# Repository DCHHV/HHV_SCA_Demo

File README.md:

# DEF CON Hardware Hacking Village Side Channel Attack Demo
This demo focuses on teaching and exploiting a simple timing attack vulnerable set up. It is a hardware device that consists of a PIC12F1572 (Enhanced Mid-range), 4 tactile buttons, LED indicators, an FTDI USB serial interface, and a connection for a logic analyzer (specifically a USBee AX PRO which the HHV has a small stock of). The demo is self-guided, that is, the serial interface provides instructions on each stage of the demo.

## About
The demo consists of 4 stages that become increasingly difficult. Each stage requires the user to identify a valid PIN for that stage. The PIN is a 4 digit, 4 value number; this provides 256 combinations. Due to the low complexity and lack of timeout penalty, brute forcing a PIN for each stage is reasonably possible but highly discouraged since the intent is to learn about side-channel attacks.

There are two LEDs, a red and a green, that flicker when the PIN is being input. The green LED turns on when a button is pressed, and off when it is released. Depending on the stage, once the full PIN is input, the red LED will flash if the pin was incorrect, or the green LED will turn solid for a few seconds if it was correct. The USB serial interface also has a red and green LED to indicate serial activity.

The digits of the PIN are connected to a single analog input of the PIC. Between the switches, a resistor ladder is set up. This allows for a consistent and unique analog voltage value for each digit. The analog input is polled at roughly 8 ms from the PIC (this timing has no bearing on the SCA demo or its vulnerabilities).

The red and green LEDs for the PIN input are connected to a 2x5 0.1" female header. A USBee AX PRO can be directly connected to this input. The LEDs are then connected to D0 and D1 of the logic analyzer. This logic analyzer is compatible with `sigrok`/`pulseview`, it is not a Saleae clone. Any other 3.3 V compatible logic analyzers can be used instead; it was highly convenient to use this pinout as the HHV has a stock of the USBee logic analyzers.

Note that we have observed that some models of Saleae clones actually work better in `pulseview` than the official Logic software. This may be due to a number of reasons, but it was found that in the Logic software both for Windows and Linux, a Saleae clone would often fail to run at 16 MHz. This failure was followed up with a comment to lower the sample rate and try again. Under `pulseview` for both Windows and Linux however, this device performed at the 16 MHz sample rate quite reliably. The USBee AX PRO is not a Saleae clone; this observervation is provided as a reference for using other logic analyzers.

A full breakdown of each stage, how the vulnerability works, step by step instructions, and proper mitigation techniques for this specific setup, are available in `docs/README.md`

## Setup
There is a specific order to the following steps, this is due to `pulseview` recognizing the FTDI device and attempting to utilize it as a logic analyzer interface. Doing this in any other order is possible but it becomes a hassle as `pulseview` tries to consume the USB serial device, even if it is already open in some cases.

1. Connect the USBee AX PRO to the host computer
2. Open `pulseview`. The tool should automatically detect and initialize the logic analyzer, if not, it can be manually set up by scanning for 'fx2lafw' devices. Note that on Linux based systems, there is a separate firmware package for the 'fx2lafw' firmware files.
3. Connect the FTDI USB serial cable (if this is connected before `pulseview` is started, then `pulseview` may try to claim the FTDI device)
4. Open a serial terminal to the just created USB terminal at 9600 baud, 8n1.
5. Press "RESET" button on the HHV SCA Demo board; text should appear on the terminal

## Build your own
All of the PCB sources for EagleCAD are available in the `eagle/` directory. The Gerber files are available in the `eagle/out/` directory and are named directly for use with OSHPark. Simply zip up the files and upload them. The Gerber files are also compatible with pretty much every PCB manufacturer as-is. A full BOM is also in the `eagle/` directory.

The PIC _can_ be programmed via the on-board ICSP header by connecting a PICKit device which supports PIC12F1572. However, we do not recommend connecting directly to this and instead recommend programming the microcontroller out of circuit. Due to conflicting driving signals, there are two marked pads that must be cut for ICSP operation. These must be bridged back together for normal operation.

The `HHV_SCA_Demo-production.hex` file can be directly written to the PIC12F1572.

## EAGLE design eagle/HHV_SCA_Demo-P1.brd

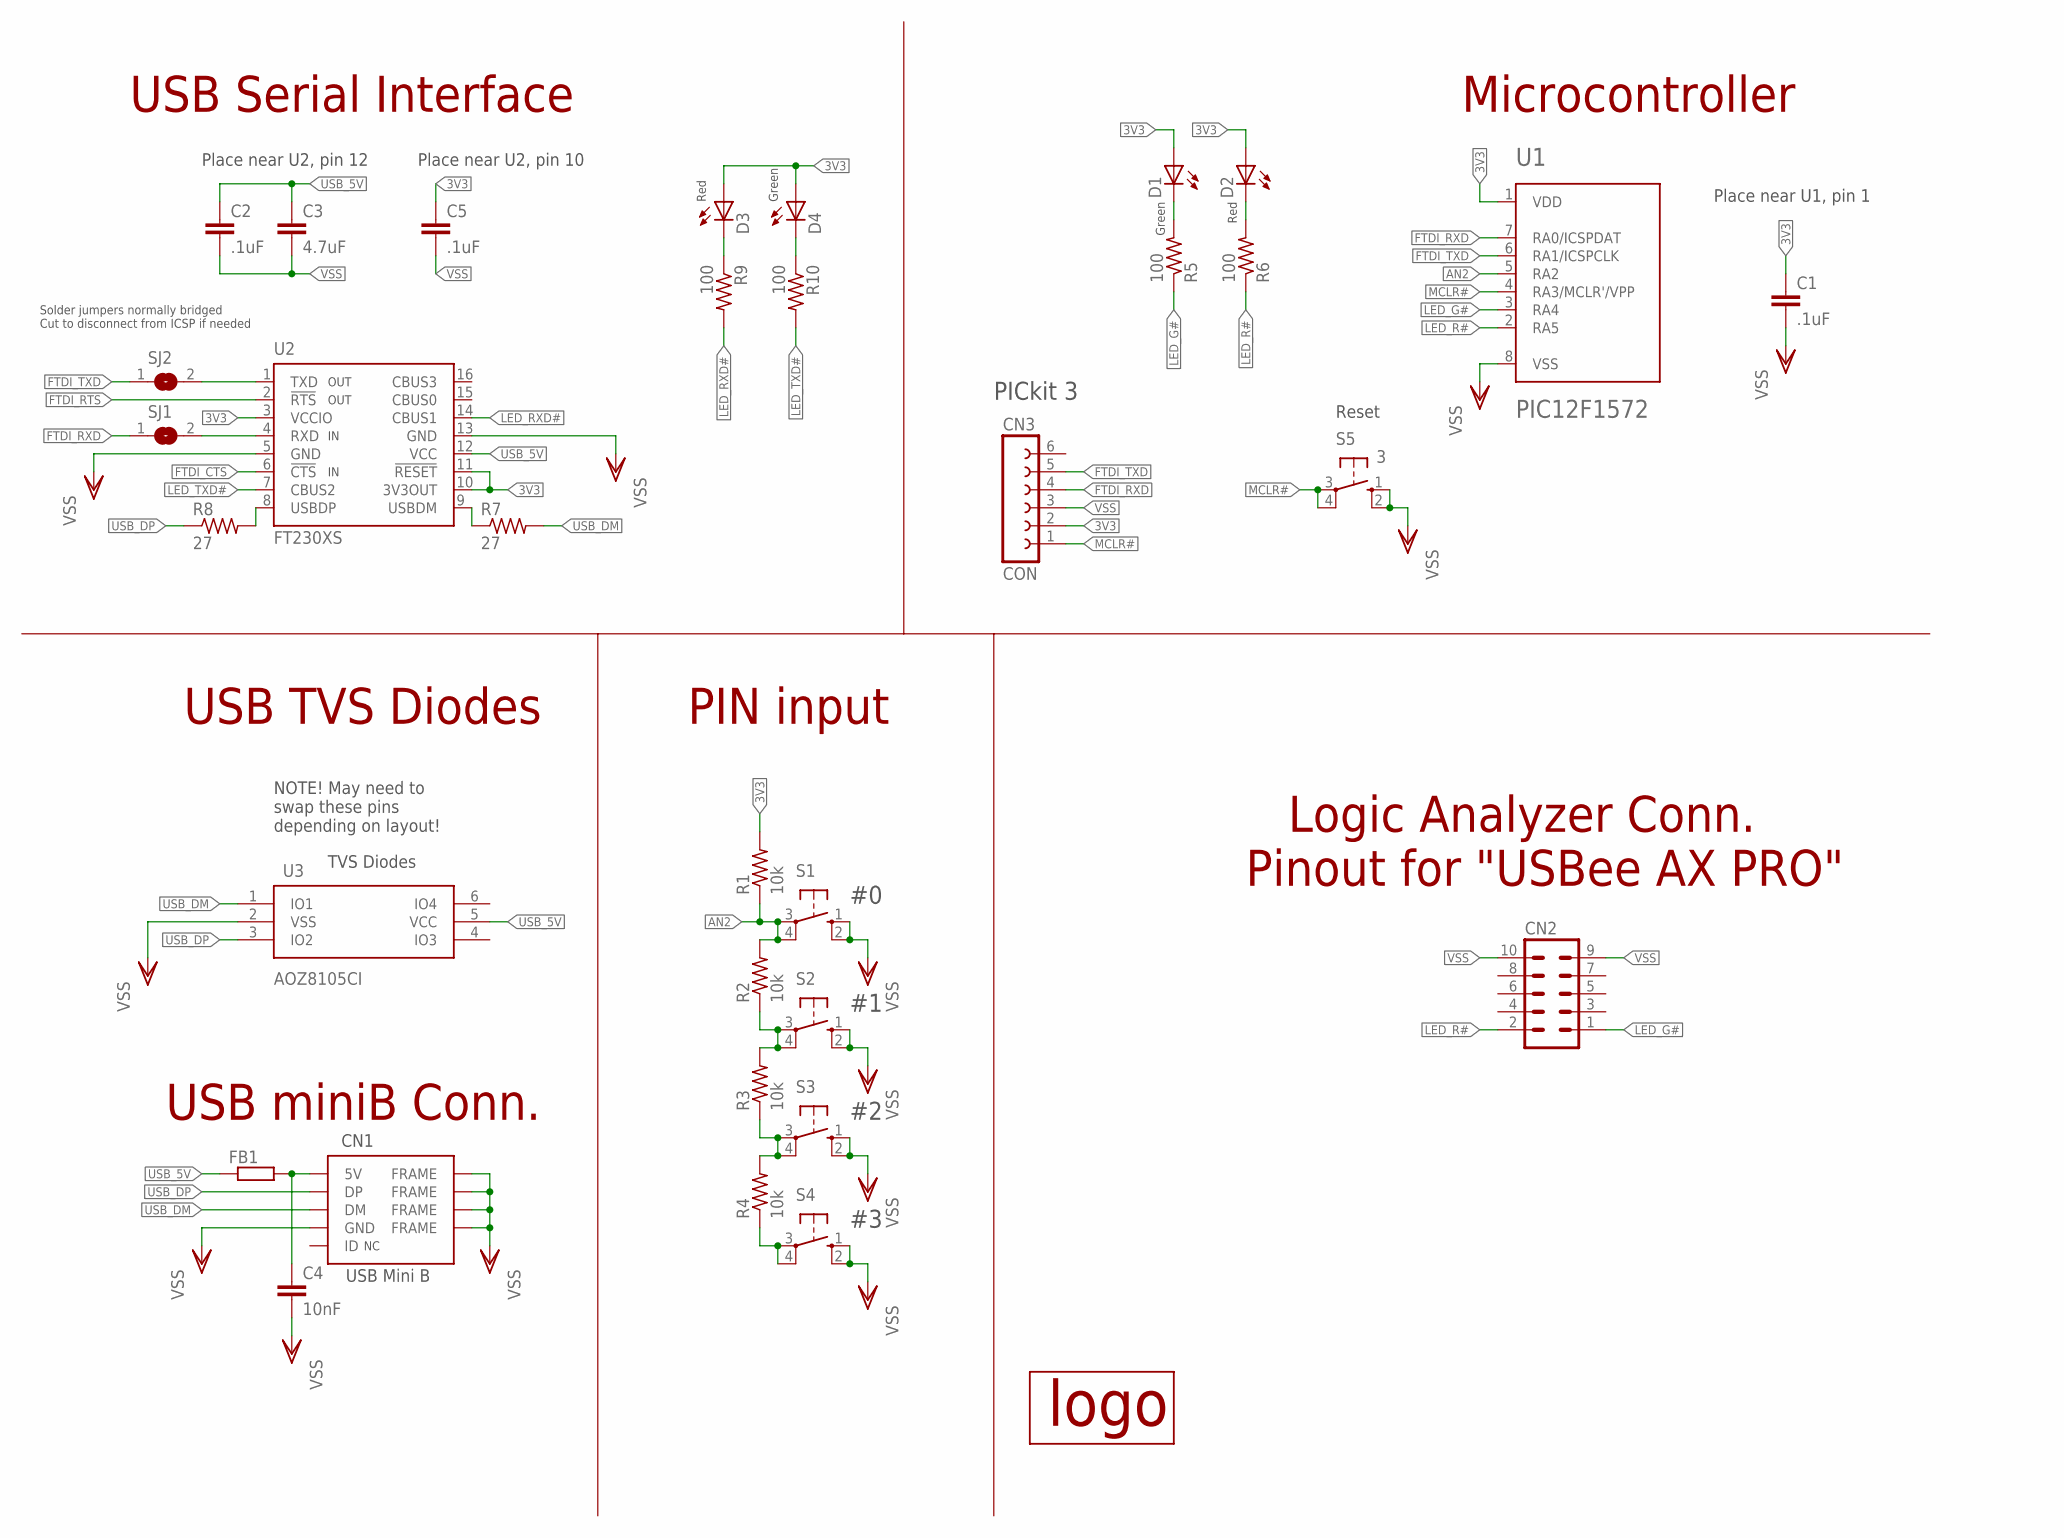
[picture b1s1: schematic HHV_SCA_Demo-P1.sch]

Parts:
C1, C2, C5: .1uF; C0603K
C3: 4.7uF; C0603K
C4: 10nF; C0603K
CN1: MINIUSB-SMD
CN2: MA05-2
CN3: CON; FE06
D1, D2, D3, D4: LED3MM
FB1: R-EU_R0603; R0603
R1, R2, R3, R4: 10k; R0603
R5, R6, R9, R10: 100; R0603
R7, R8: 27; R0402
S1, S2, S3, S4: 10-XX; B3F-10XX
S5: 3; B3F-10XX
SJ1, SJ2: SJ
U1: PIC12F1572; DIL8
U2: FT230XS; SSOP16
U3: AOZ8105CI; SOT23-6L
U$1: KBELOGO-SILK

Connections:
3V3: C1.1, C5.1, CN3.2, D1.A, D2.A, D3.A, D4.A, R1.2, U1.1 (VDD), U2.3 (VCCIO), U2.10 (3V3OUT), U2.11 (!RESET)
AN2: R1.1, R2.2, S1.3, S1.4 (P1), U1.5 (RA2)
FTDI_CTS: U2.6 (!CTS)
FTDI_RTS: U2.2 (!RTS)
FTDI_RXD: CN3.4, SJ1.1, U1.7 (RA0/ICSPDAT)
FTDI_TXD: CN3.5, SJ2.1, U1.6 (RA1/ICSPCLK)
LED_G#: CN2.1, R5.1, U1.3 (RA4)
LED_R#: CN2.2, R6.1, U1.2 (RA5)
LED_RXD#: R9.2, U2.14 (CBUS1)
LED_TXD#: R10.2, U2.7 (CBUS2)
MCLR#: CN3.1, S5.3, S5.4 (P1), U1.4 (RA3/MCLR'/VPP)
unnamed: R4.1, S4.3, S4.4 (P1)
unnamed: R3.1, R4.2, S3.3, S3.4 (P1)
unnamed: D2.K (C), R6.2
unnamed: R7.1, U2.9 (USBDM)
unnamed: R2.1, R3.2, S2.3, S2.4 (P1)
unnamed: R8.2, U2.8 (USBDP)
unnamed: D1.K (C), R5.2
unnamed: D3.K (C), R9.1
unnamed: C4.1, CN1.5V, FB1.2
unnamed: D4.K (C), R10.1
unnamed: SJ2.2, U2.1 (TXD)
unnamed: SJ1.2, U2.4 (RXD)
USB_5V: C2.1, C3.1, FB1.1, U2.12 (VCC), U3.5 (VCC)
USB_DM: CN1.USB_DM (DM), R7.2, U3.1 (IO1)
USB_DP: CN1.USB_DP (DP), R8.1, U3.3 (IO2)
VSS: C1.2, C2.2, C3.2, C4.2, C5.2, CN1.GND@0 (FRAME), CN1.GND@1 (FRAME), CN1.GND@2 (FRAME), CN1.GND@3 (FRAME), CN1.VSS (GND), CN2.9, CN2.10, CN3.3, S1.1 (S), S1.2 (S1), S2.1 (S), S2.2 (S1), S3.1 (S), S3.2 (S1), S4.1 (S), S4.2 (S1), S5.1 (S), S5.2 (S1), U1.8 (VSS), U2.5 (GND), U2.13 (GND), U3.2 (VSS)

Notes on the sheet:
OUT
Place near U2, pin 12
TVS Diodes
Place near U2, pin 10
CN1
USB Mini B
NOTE! May need to swap these pins depending on layout!
Red
Green
PICkit 3
Place near U1, pin 1
USB Serial Interface
USB TVS Diodes
USB miniB Conn.
Microcontroller
Reset
PIN input
Logic Analyzer Conn. Pinout for "USBee AX PRO"
Solder jumpers normally bridged Cut to disconnect from ICSP if needed

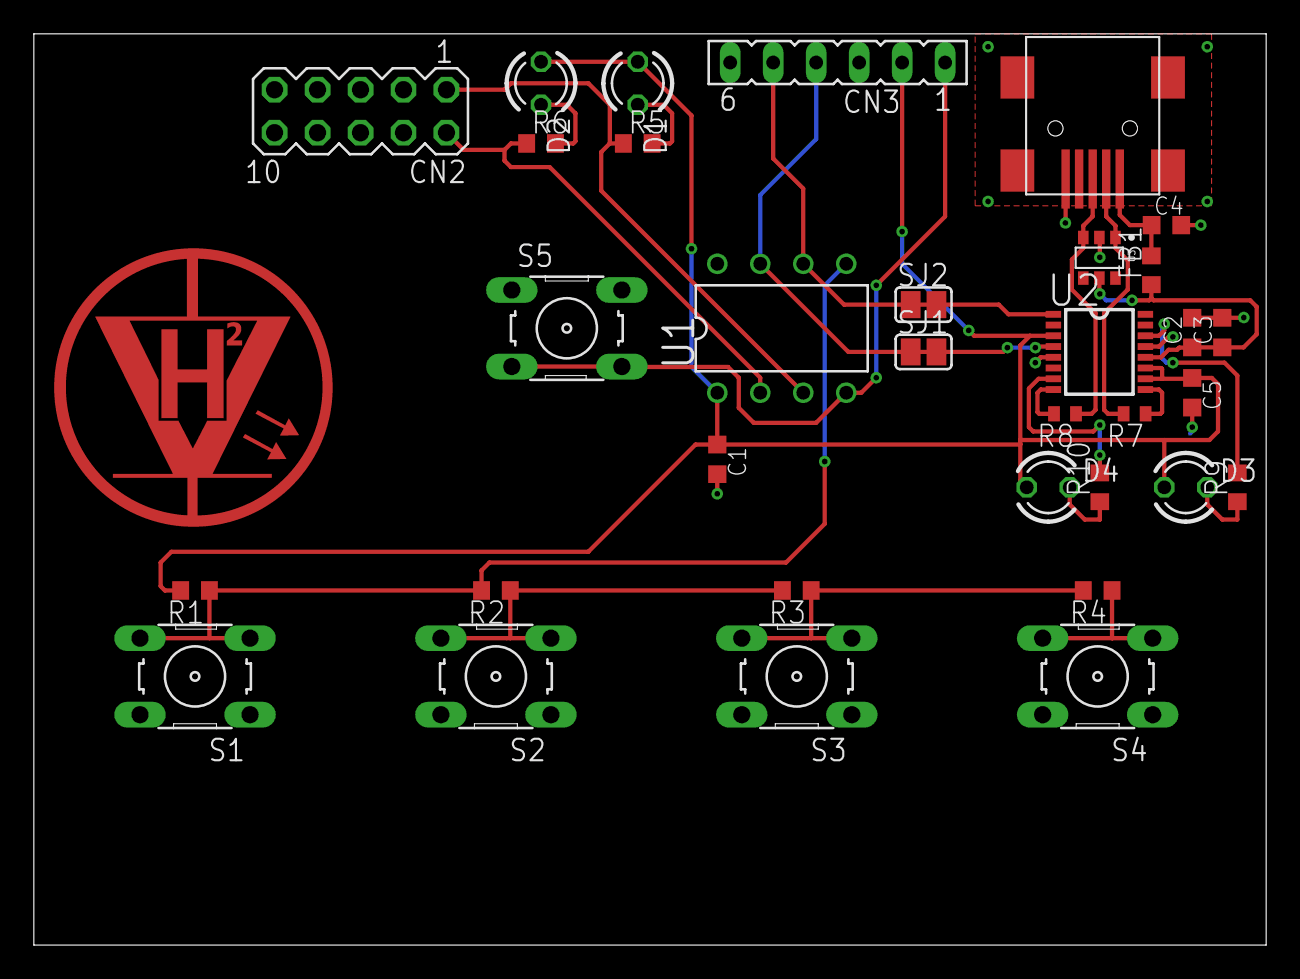
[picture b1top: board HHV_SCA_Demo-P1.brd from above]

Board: 2 copper layers, 72.8 x 53.8 mm, 34 parts (1 on the bottom side), 25 nets.

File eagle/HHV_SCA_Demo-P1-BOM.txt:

Qty Value        Device       Package      Parts                   Description                
1                R-EU_R0603   R0603        FB1                     FERRITE BEAD
2   27           R-US_R0402   R0402        R7, R8                  RESISTOR
4   100          R-US_R0603   R0603        R5, R6, R9, R10         RESISTOR
4   10k          R-US_R0603   R0603        R1, R2, R3, R4          RESISTOR
1   10nF         C-EUC0603K   C0603K       C4                      CAPACITOR
3   .1uF         C-EUC0603K   C0603K       C1, C2, C5              CAPACITOR
1   4.7uF        C-EUC0603K   C0603K       C3                      CAPACITOR
1   AOZ8105CI    AOZ8105CI    SOT23-6L     U3                      TVS
1                FE06-1       FE06         CN3                     FEMALE HEADER              
1                MA05-2       MA05-2       CN2                     PIN HEADER                 
1   FT230XS      FT230XS      SSOP16       U2                      USB to BASIC UART IC       
1   MINIUSB-SMD  MINIUSB-SMD  MINIUSB-SMD  CN1                     EDAC 690-005-299-043       
1   PIC12F1572   PIC12F1571   DIL8         U1                      PIC12F1571/2               
2   RED          LED3MM       LED3MM       D2, D3                  LED                        
2   GRN          LED3MM       LED3MM       D1, D4                  LED                        
5                10-XX        B3F-10XX     SW1, SW2, SW3, SW4, SW5 OMRON SWITCH

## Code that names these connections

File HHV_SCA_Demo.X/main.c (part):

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#pragma config FOSC = INTOSC  // INTOSC oscillator: I/O function on CLKIN pin.
#pragma config WDTE = OFF     // Watchdog Timer disable.
#pragma config PWRTE = OFF    // Power-up Timer enbable.
#pragma config MCLRE = ON     // MCLR/VPP pin function is MCLR.
#pragma config CP = OFF       // Program memory code protection disabled.
#pragma config BOREN = ON     // Brown-out Reset enabled.
#pragma config CLKOUTEN = OFF // CLKOUT function is disabled; I/O or oscillator function on the CLKOUT pin.
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volatile uint8_t loop __at(0x78);
volatile uint8_t cmp __at(0x79);

#define LED_G 4
#define LED_R 5

extern const char intro_text[];
extern const char stage_0_text[];
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  TRISAbits.TRISA2 = 1;
  
  /* LEDs as outputs, active low */
  PORTAbits.RA4 = 1;
  PORTAbits.RA5 = 1;
  TRISAbits.TRISA4 = 0;
  TRISAbits.TRISA5 = 0;
}
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
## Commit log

2019-06-20 Initial commit of files for safe keeping
    Schematic is mostly done, pending final review
    Layout is still WIP
    Datasheet PDFs added for ICs
2019-06-30 eagle: Final iteration of P1 rev
    Need to do another pass before final gerber output
2019-06-30 eagle: Added OSHPark design rule file
    Has been slightly modified to round pads, tent vias, set pin 1 TH
    to square, increase isolation
2019-06-30 eagle: Added OSHPark CAM file
2019-06-30 eagle: Finalized schematic and board files
    Added donation text to back silkscreen
    Changed schematic names of S* to SW*
    Removed value from SW5
    Added color values to D*
2019-06-30 eagle: out: Added gerber files, named with OSHPark extensions
    Added Gerbv project file
2019-06-30 eagle: Added BOM
2019-07-01 docs: Added PCB top and bottom photos
    Derived from OSHPark's automatic tools
2019-07-30 tools: Initial commit of tools
    Added pin_predictor.c, string_packer.c, makefile, and gitignore
2019-07-30 eagle: Final draft of P1 rev
2019-07-30 texts: Added text files, gitignore, and output script
    Final draft of texts for the SCA Demo
2019-08-14 PIC: Initial commit of firmware, final draft
    Text based on commit 52b2d72f35758e9e11d60abb7e8b3664e2fdf898
    Added output hex file
2019-08-14 LICENSE: Add license
2019-08-26 proper_compare: Fixed typo in comments
2019-08-27 README: Added main README with description
    docs: writeup: Added initial writeup of whole application.
2019-08-27 README: Updated writeup file location
2019-08-28 docs: writeup: Moved to README
    Cleaned up formatting of asm
    Updated with good Stage 2 text
    Added photos for Stage 1
2019-08-28 docs: Added photos of Stage 1 captures
    Pulseview window capture of a correct and incorrect first digit
2019-08-28 tools: README: Added README for the tools
2019-08-28 texts: README: Added README for texts
2019-08-29 README: Added notes, also info about PCB files
    Added observational note about Saleae clones working better with pulseview
    Added information about building a copy of the whole device
2020-02-16 texts: Modified/reduced/corrected texts
    Updated strings.s from these
2020-02-16 main: Added clr_term(), update comments
2020-02-16 README: Added note
2020-02-16 proper_compare: Optimize, clean up comments
2020-02-16 docs: README: Updated content
    Clarified stage 2 nop workaround and why
    Updated code to reflect the optimizations made for stage 3
2020-02-16 proper_compare: Convert to UNIX newlines
    It was bothering me
2020-02-16 hex: Updated production hex from latest build

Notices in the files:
HHV_SCA_Demo.X/main.c:
SPDX-License-Identifier: BSD-2-Clause
Copyright (c) 2019 KBEmbedded and DEF CON Hardware Hacking Village
